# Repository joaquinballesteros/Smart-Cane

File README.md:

# Smart Cane

Smart-cane is an open hardware and open software project created to promoting an active ageing. This project was created on [Integrated Systems Engineering group](www.grupoisis.uma.es/), on Department of Electronic Technology (Málaga University). Nowadays, it is carried out at MDH University at the [Biomedical Engineering group](http://www.es.mdh.se/research-groups/32-Biomedical_Engineering) in collaboration with [Integrated Systems Engineering group](www.grupoisis.uma.es/).

The project is led by [Dr. Ballesteros](https://www.researchgate.net/profile/Joaquin_Ballesteros) and it counts with the help of [M.Sc. Alberto Tudela](https://duma.uma.es/duma/buscador/persona/535571bb-1da1-4cbd-a49a-7b0d61c4cd2d/), [B.Sc. Juan Caro](https://duma.uma.es/duma/buscador/persona/6eeb9474-2ce9-4c46-8f6d-ff7827abb2c9/) and the support of [Prof. Dr. Maria Lindén](http://www.es.mdh.se/staff/114-Maria_Lind__n) and [Prof. Dr. Cristina Urdiales](https://www.researchgate.net/profile/Cristina_Urdiales2).

This project is focused on adding on-board sensors to the cane to monitor users. These sensors should be affordable in order to reduce the cost and to increase the number of end users. Force sensors and hall effect sensors are being testing to measure the weight-bearing and other significant parameters related with an active ageing. The results are been validated in collaboration with the following Senior centres (Centros de participación activa) in Córdoba (Spain): CÓRDOBA II, FUENSANTA – CAÑERO, PONIENTE, LOS NARANJOS.

## Built With
* [Fusion 360](https://www.autodesk.com/products/fusion-360/overview) - The program used to to design the plastic pieces. All these documents have been exported to STEP file extension too. It is an ISO standard exchange format that can be openned by other programs, such as [FreeCAD](https://github.com/FreeCAD/FreeCAD).

* [MBED online compiler](https://os.mbed.com/handbook/mbed-Compiler) - The online program used to to programming the BLE Nano v1 microcontroller. 

* [Android Studio](https://developer.android.com/studio/) - The program to create the mobile software.

## Authors

* **Joaquín Ballesteros** - *Team leader, design and programming* - [joaquinballesteros](https://github.com/joaquinballesteros)
* **Alberto Tudela** - *Electronic and 3D models* - [ajtudela](https://github.com/ajtudela)
* **Juan Caro** - *Electronic and software* - [jrcaro](https://github.com/jrcaro)

Contact: jballesteros@uma.es

## Contributors

* Swedish Knowledge Foundation (KKS) through the research profile [Embedded Sensor Systems for Health at Mälardalen University](https://www.mdh.se/forskning/inriktningar/inbyggda-system/ess-h?l=en_UK), Sweden - [Prof. Dr. Maria Lindén](http://www.es.mdh.se/staff/114-Maria_Lind__n).

* [Plan Propio de la Universidad de Málaga (Proyectos Puente)](https://www.uma.es/servicio-de-investigacion/cms/menu/plan-propio-de-investigacion/?set_language=en) at Málaga University, Spain -  [Prof. Dr. Cristina Urdiales](https://www.researchgate.net/profile/Cristina_Urdiales2).

## License

This project is licensed under the Creative Commons Attribution 4.0 - see the [LICENSE.md](https://github.com/joaquinballesteros/Smart-Cane/blob/master/LICENSE) file for details.

## Acknowledgments

The authors would like to thank to [Ms. Luna Ruiz](http://lunakageyama.blogspot.com/) who greatly assisted every single test.

## Publications
Ballesteros, J., Tudela, A., Caro-Romero, J. R., & Urdiales, C. (2019). Weight-bearing estimation for cane users by using onboard sensors. Sensors, 19(3), 509. [link](https://www.mdpi.com/1424-8220/19/3/509/htm)

Ballesteros, J., Tudela, A., Caro-Romero, J. R., & Urdiales, C. (2019, May). A cane-based low cost sensor to implement attention mechanisms in telecare robots. In 2019 International Conference on Robotics and Automation (ICRA) (pp. 1473-1478). IEEE.[link](https://ieeexplore.ieee.org/document/8794283)

Caro-Romero, J. R., Ballesteros, J., Garcia-Lagos, F., Urdiales, C., & Sandoval, F. (2019, June). A Neural Network for Stance Phase detection in smart cane users. In International Work-Conference on Artificial Neural Networks (pp. 310-321). Springer, Cham.[link](https://link.springer.com/chapter/10.1007/978-3-030-20521-8_26)

Ayala, I., Ballesteros, J., Caro-Romero, J. R., Amor, M., & Fuentes, L. (2019). Self-Adaptation of mHealth Devices: The Case of the Smart Cane Platform. In Multidisciplinary Digital Publishing Institute Proceedings (Vol. 31, No. 1, p. 23).[link](https://www.mdpi.com/2504-3900/31/1/23)

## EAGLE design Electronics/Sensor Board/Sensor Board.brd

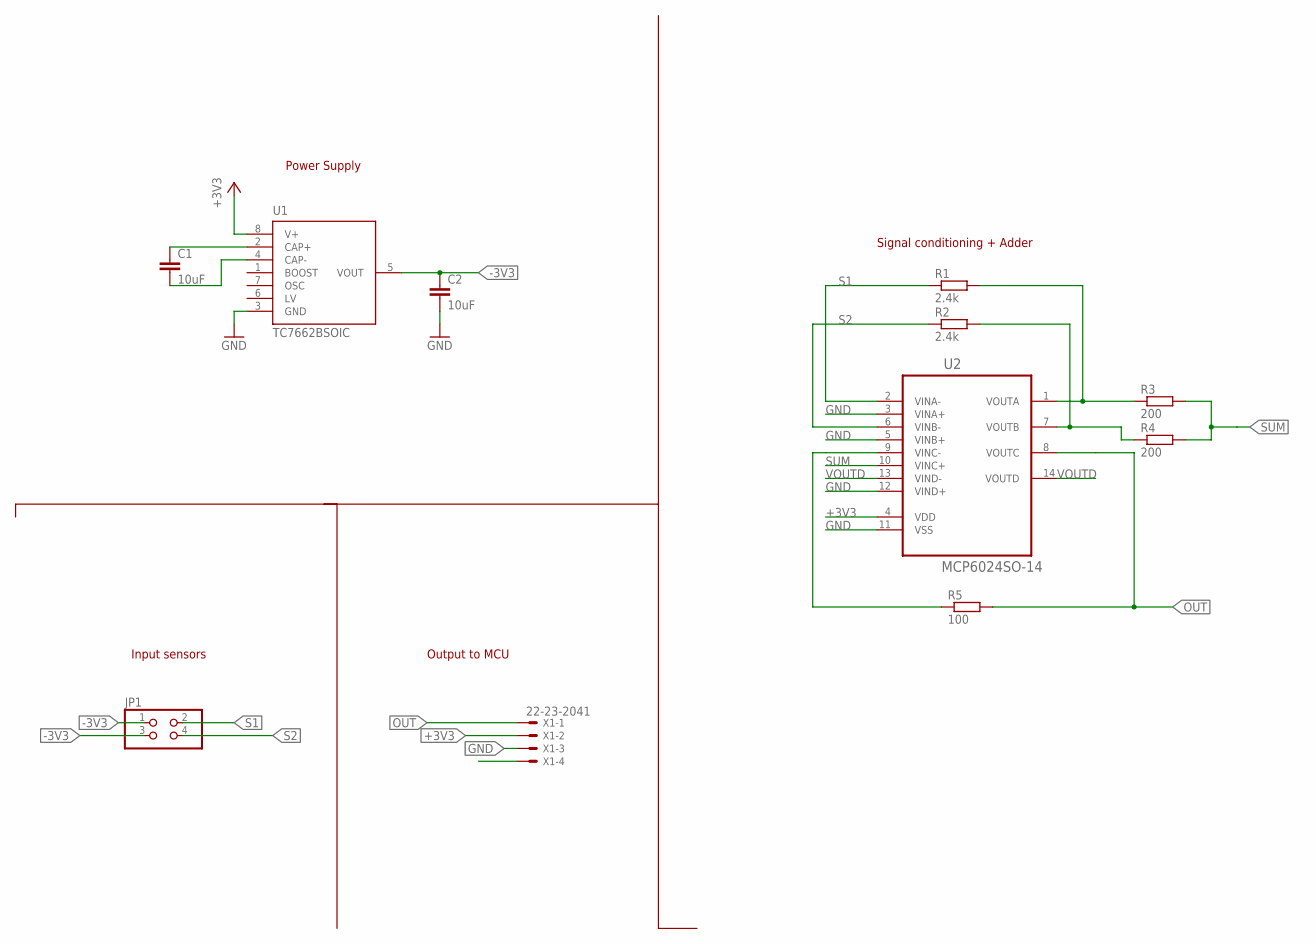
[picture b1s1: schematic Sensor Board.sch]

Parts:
C1, C2: 10uF; C0603
JP1: PINHD-2X2/90; 2X02/90
R1, R2: 2.4k; R0603
R3, R4: 200; R0603
R5: 100; R0603
U1: TC7662BSOIC; SO-08
U2: MCP6024SO-14; SO-14
X1: 22-23-2041

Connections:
+3V3: U1.8 (V+), U2.4 (VDD), X1.2
-3V3: C2.1, JP1.1, JP1.3, U1.5 (VOUT)
GND: C2.2, U1.3 (GND), U2.3 (VINA+), U2.5 (VINB+), U2.11 (VSS), U2.12 (VIND+), X1.3
unnamed: C1.1, U1.2 (CAP+)
unnamed: C1.2, U1.4 (CAP-)
unnamed: R1.2, R3.1, U2.1 (VOUTA)
unnamed: R2.2, R4.1, U2.7 (VOUTB)
unnamed: R5.1, U2.9 (VINC-)
OUT: R5.2, U2.8 (VOUTC), X1.1
S1: JP1.2, R1.1, U2.2 (VINA-)
S2: JP1.4, R2.1, U2.6 (VINB-)
SUM: R3.2, R4.2, U2.10 (VINC+)
VOUTD: U2.13 (VIND-), U2.14 (VOUTD)

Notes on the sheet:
Power Supply
Signal conditioning + Adder
Input sensors
Output to MCU

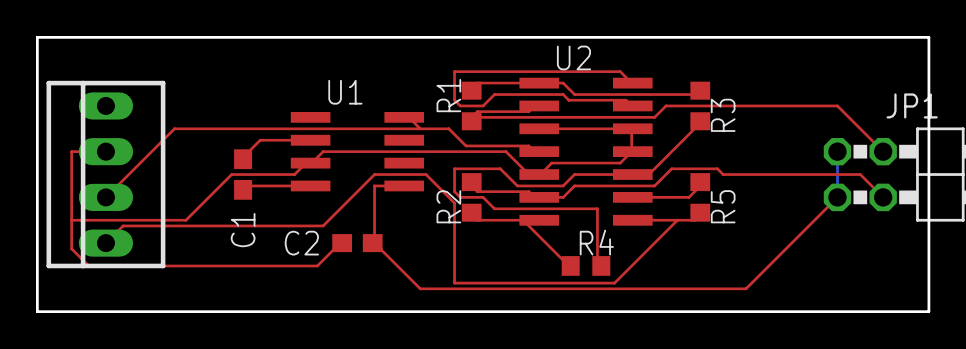
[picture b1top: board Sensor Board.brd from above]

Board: 2 copper layers, 49.5 x 15.2 mm, 11 parts (0 on the bottom side), 13 nets.

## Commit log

2018-07-25 Added CAD files
2018-07-25 Added schematics and pcb for sensor board
2018-07-26 Added datasheets files
2018-07-26 Change in schematics for better reading
2018-09-03 Added mbed code for BLE nano
2018-09-03 Modify .gitignore to read .lib files
2018-09-03 Add .lib files
2018-09-04 Update LICENSE
2018-09-12 Android application for Smart-Cane
2018-09-12 Remove BLE App folder
2018-09-12 Android App for Smart-Cane
2020-03-11 Adding a test file by console
2020-03-11 meneasje
2020-03-11 mensaje
2022-11-07 Update README.md
    Cambio afiliación.

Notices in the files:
README.md:
License: CC BY 4.0
